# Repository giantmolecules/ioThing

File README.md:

# ioThing

## SAIC Model 2 Object Fall 2018

###test

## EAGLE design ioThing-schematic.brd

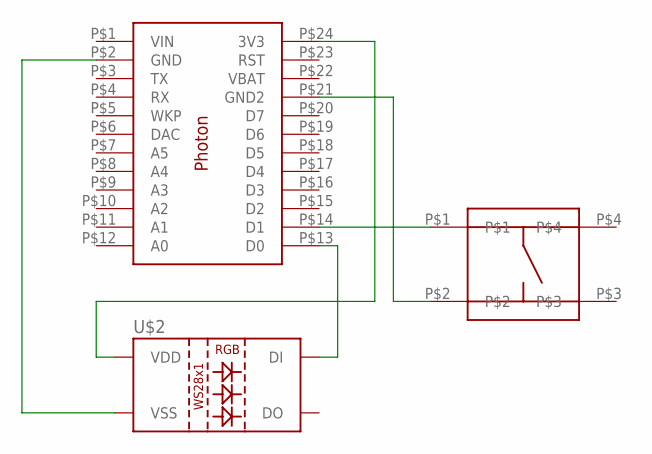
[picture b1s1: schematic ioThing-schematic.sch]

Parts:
U$1: PHOTON
U$2: 5MM-NEOPIXEL; T1-3/4-LED
U$3: TACTILE_SWITCH

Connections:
unnamed: U$1.P$24 (3V3), U$2.P$2 (VDD)
unnamed: U$1.P$2 (GND), U$2.P$3 (VSS)
unnamed: U$1.P$13 (D0), U$2.P$1 (DI)
unnamed: U$1.P$14 (D1), U$3.P$1
unnamed: U$1.P$21 (GND2), U$3.P$2

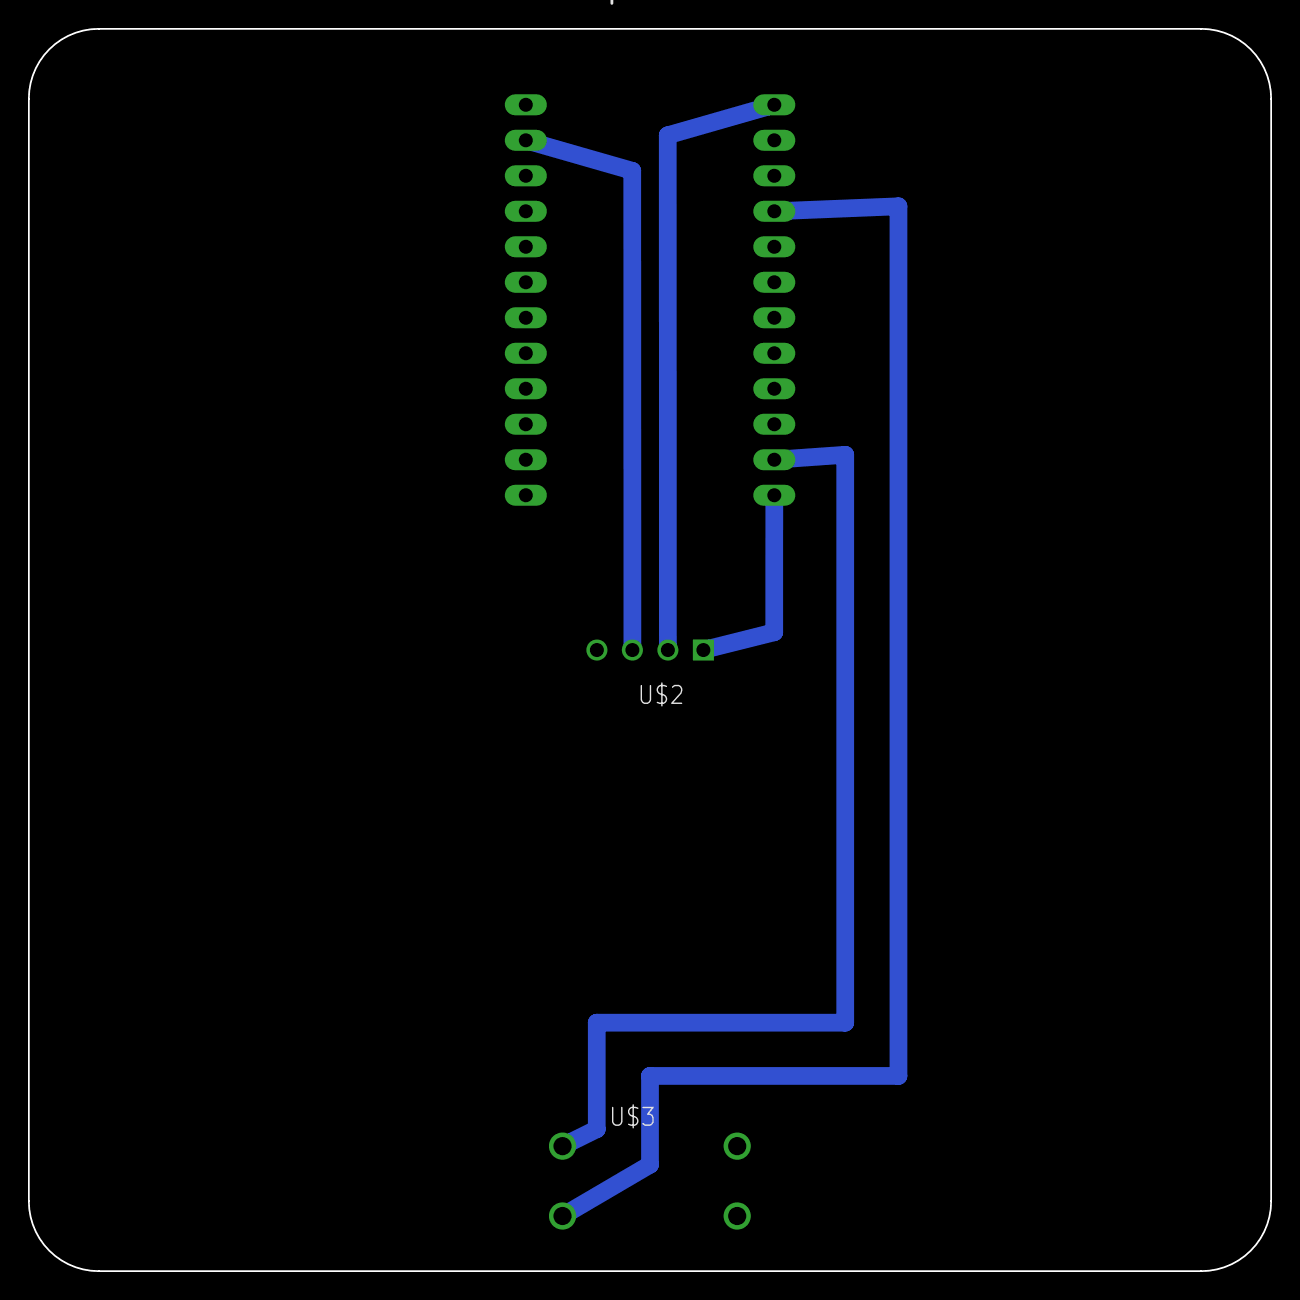
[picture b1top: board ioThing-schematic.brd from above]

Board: 2 copper layers, 88.9 x 88.9 mm, 3 parts (0 on the bottom side), 5 nets.

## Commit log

2018-09-20 init
2018-09-20 adding switch image
2018-09-20 add led
2018-10-04 works!
2018-10-04 dome
